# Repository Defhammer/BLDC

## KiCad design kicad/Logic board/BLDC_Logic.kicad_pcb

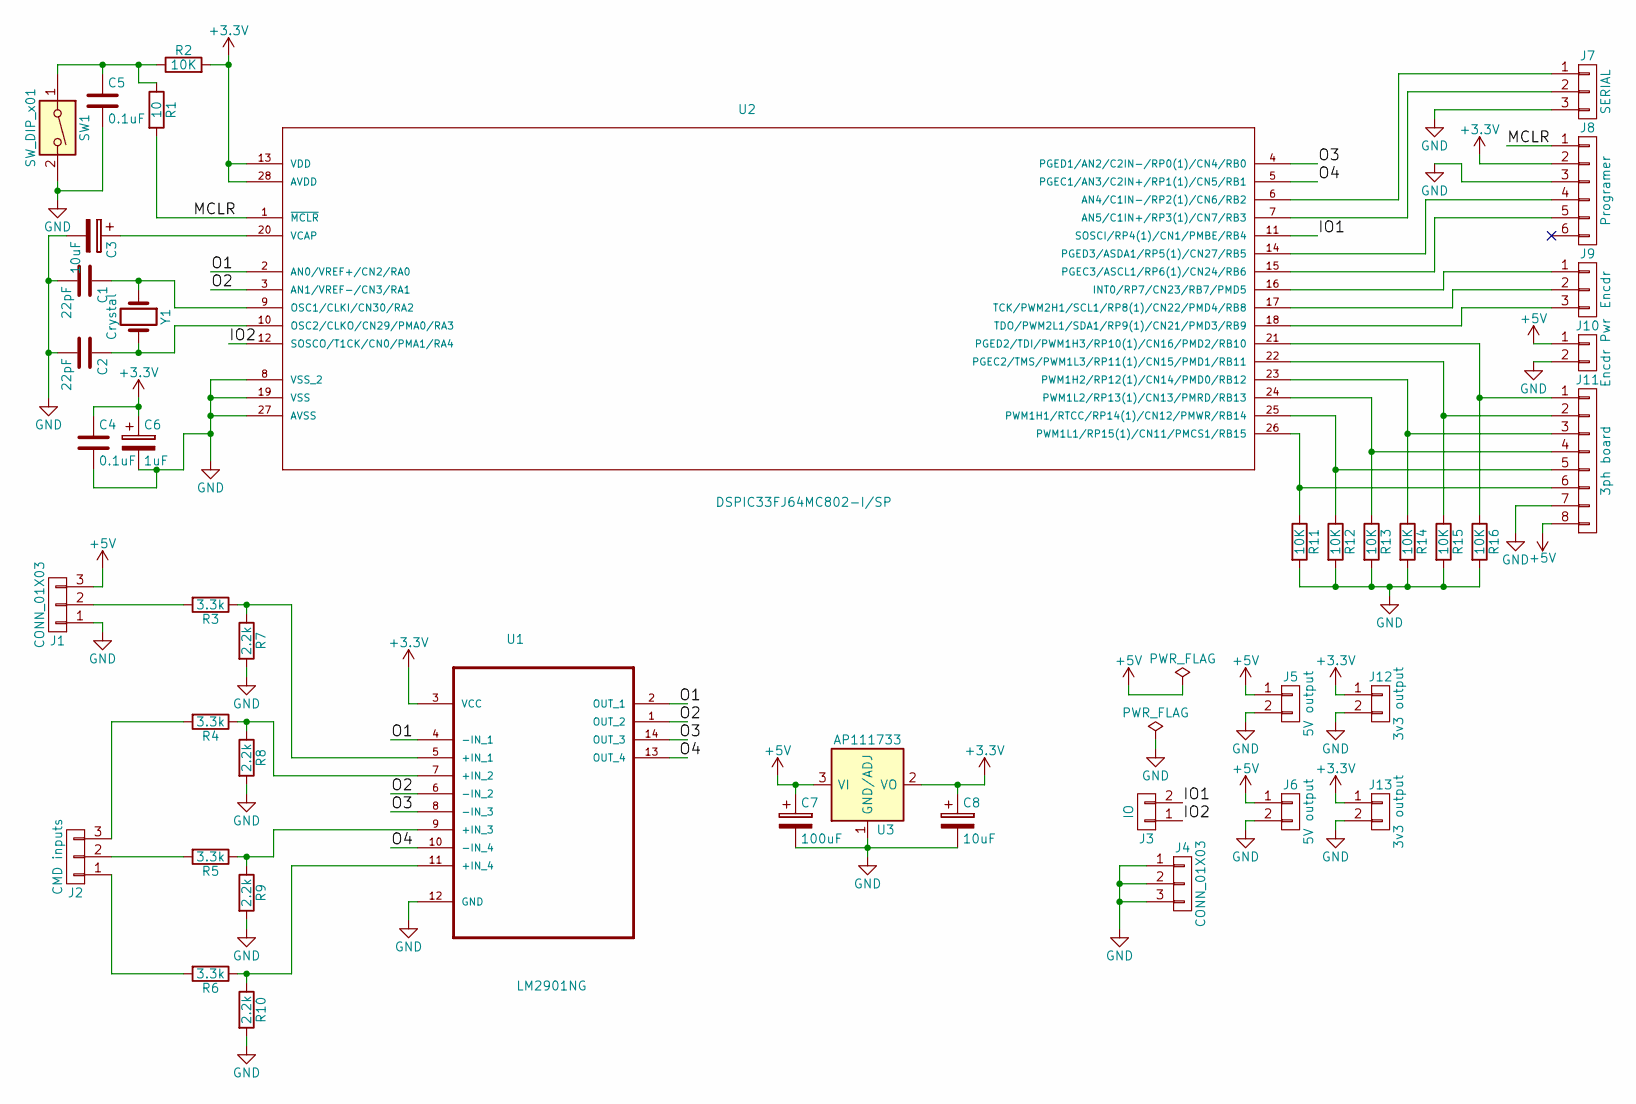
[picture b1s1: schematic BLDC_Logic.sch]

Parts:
C1, C2: 22pF; C_Disc_D3.0mm_W1.6mm_P2.50mm
C3: 10uF; CP_Radial_D4.0mm_P1.50mm
C4, C5: 0.1uF; C_Disc_D3.0mm_W2.0mm_P2.50mm
C6: 1uF; CP_Radial_D4.0mm_P2.00mm
C7: 100uF; CP_Radial_D6.3mm_P2.50mm
C8: 10uF; CP_Radial_D4.0mm_P2.00mm
J1, J4: CONN_01X03; Pin_Header_Straight_1x03_Pitch2.54mm
J2: CMD inputs; Pin_Header_Straight_1x03_Pitch2.54mm
J3: IO; Pin_Header_Straight_1x02_Pitch2.54mm
J5, J6: 5V output; Pin_Header_Straight_1x02_Pitch2.54mm
J7: SERIAL; Pin_Header_Straight_1x03_Pitch2.54mm
J8: Programer; Pin_Header_Straight_1x06_Pitch2.54mm
J9: Encdr; Pin_Header_Straight_1x03_Pitch2.54mm
J10: Encdr Pwr; Pin_Header_Straight_1x02_Pitch2.54mm
J11: 3ph board; Pin_Header_Straight_1x08_Pitch2.54mm
J12, J13: 3v3 output; Pin_Header_Straight_1x02_Pitch2.54mm
R1: 10; R_Axial_DIN0204_L3.6mm_D1.6mm_P7.62mm_Horizontal
R2, R11, R12, R13, R14, R15, R16: 10K; R_Axial_DIN0204_L3.6mm_D1.6mm_P7.62mm_Horizontal
R3, R4, R5, R6: 3.3k; R_Axial_DIN0204_L3.6mm_D1.6mm_P7.62mm_Horizontal
R7, R8, R9, R10: 2.2k; R_Axial_DIN0204_L3.6mm_D1.6mm_P7.62mm_Horizontal
SW1: SW_DIP_x01; SW_PUSH_6mm
U1: LM2901NG; DIP-14_W7.62mm
U2: DSPIC33FJ64MC802-I/SP; DIP254P762X508-28
U3: AP111733; TO-220_Vertical
Y1: Crystal; Crystal_HC49-U_Vertical

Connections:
+3V3: C4.1, C6.1, C8.1, J8.2, J12.1, J13.1, R2.2, U1.3 (VCC), U2.13 (VDD), U2.28 (AVDD), U3.2 (VO), U3.4 (VO)
+5V: C7.1, J1.3, J5.1, J6.1, J10.1, J11.8, U3.3 (VI)
/IO1: J3.2, U2.11 (SOSCI/RP4(1)/CN1/PMBE/RB4)
/IO2: J3.1, U2.12 (SOSCO/T1CK/CN0/PMA1/RA4)
/MCLR: J8.1, R1.2, U2.1 (~MCLR)
/O1: U1.2 (OUT_1), U1.4 (-IN_1), U2.2 (AN0/VREF+/CN2/RA0)
/O2: U1.1 (OUT_2), U1.6 (-IN_2), U2.3 (AN1/VREF-/CN3/RA1)
/O3: U1.8 (-IN_3), U1.14 (OUT_3), U2.4 (PGED1/AN2/C2IN-/RP0(1)/CN4/RB0)
/O4: U1.10 (-IN_4), U1.13 (OUT_4), U2.5 (PGEC1/AN3/C2IN+/RP1(1)/CN5/RB1)
GND: C1.2, C2.2, C3.2, C4.2, C5.2, C6.2, C7.2, C8.2, J1.1, J4.1, J4.2, J4.3, J5.2, J6.2, J7.3, J8.3, J10.2, J11.7, J12.2, J13.2, R7.2, R8.2, R9.2, R10.2, R11.2, R12.2, R13.2, R14.2, R15.2, R16.2, SW1.2, U1.12 (GND), U2.8 (VSS_2), U2.19 (VSS), U2.27 (AVSS), U3.1 (GND/ADJ)
unnamed: C1.1, U2.9 (OSC1/CLKI/CN30/RA2), Y1.1
unnamed: C2.1, U2.10 (OSC2/CLKO/CN29/PMA0/RA3), Y1.2
unnamed: C3.1, U2.20 (VCAP)
unnamed: C5.1, R1.1, R2.1, SW1.1
unnamed: J1.2, R3.2
unnamed: J2.1, R6.2
unnamed: J2.2, R5.2
unnamed: J2.3, R4.2
unnamed: J7.1, U2.6 (AN4/C1IN-/RP2(1)/CN6/RB2)
unnamed: J7.2, U2.7 (AN5/C1IN+/RP3(1)/CN7/RB3)
unnamed: J8.4, U2.14 (PGED3/ASDA1/RP5(1)/CN27/RB5)
unnamed: J8.5, U2.15 (PGEC3/ASCL1/RP6(1)/CN24/RB6)
unnamed: J9.1, U2.16 (INT0/RP7/CN23/RB7/PMD5)
unnamed: J9.2, U2.17 (TCK/PWM2H1/SCL1/RP8(1)/CN22/PMD4/RB8)
unnamed: J9.3, U2.18 (TDO/PWM2L1/SDA1/RP9(1)/CN21/PMD3/RB9)
unnamed: J11.1, R16.1, U2.21 (PGED2/TDI/PWM1H3/RP10(1)/CN16/PMD2/RB10)
unnamed: J11.2, R15.1, U2.22 (PGEC2/TMS/PWM1L3/RP11(1)/CN15/PMD1/RB11)
unnamed: J11.3, R14.1, U2.23 (PWM1H2/RP12(1)/CN14/PMD0/RB12)
unnamed: J11.4, R13.1, U2.24 (PWM1L2/RP13(1)/CN13/PMRD/RB13)
unnamed: J11.5, R12.1, U2.25 (PWM1H1/RTCC/RP14(1)/CN12/PMWR/RB14)
unnamed: J11.6, R11.1, U2.26 (PWM1L1/RP15(1)/CN11/PMCS1/RB15)
unnamed: R3.1, R7.1, U1.5 (+IN_1)
unnamed: R4.1, R8.1, U1.7 (+IN_2)
unnamed: R5.1, R9.1, U1.9 (+IN_3)
unnamed: R6.1, R10.1, U1.11 (+IN_4)

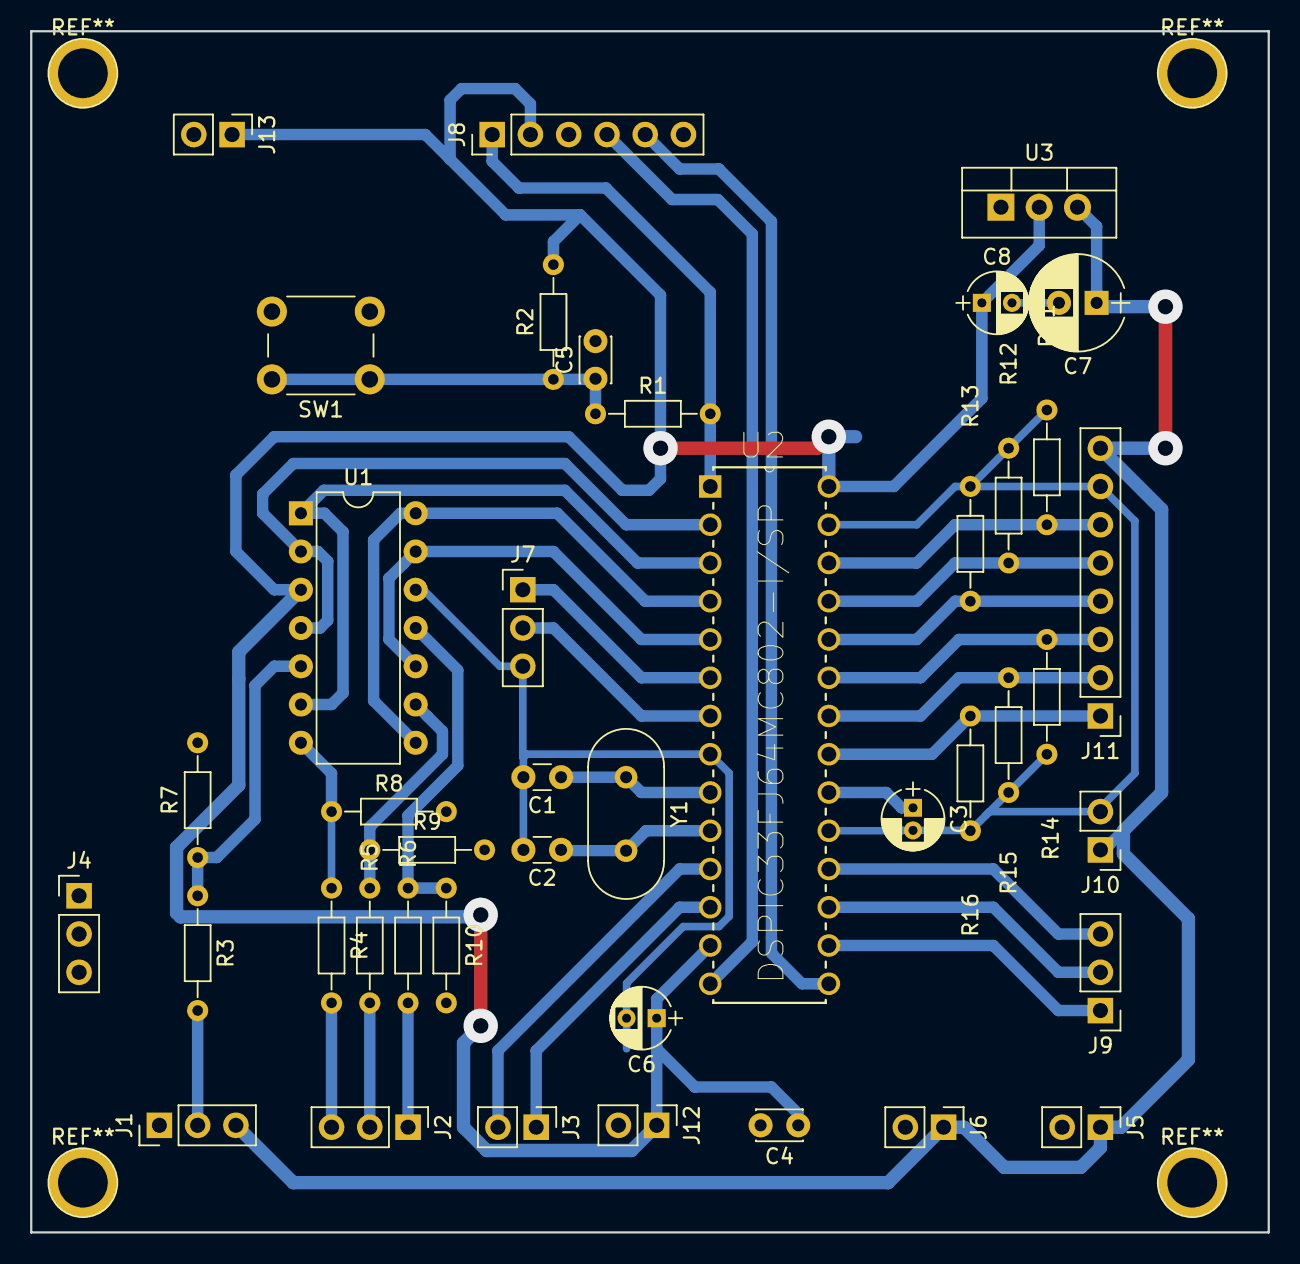
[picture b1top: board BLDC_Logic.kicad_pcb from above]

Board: 2 copper layers, 82.2 x 79.8 mm, 42 parts (0 on the bottom side), 35 nets.

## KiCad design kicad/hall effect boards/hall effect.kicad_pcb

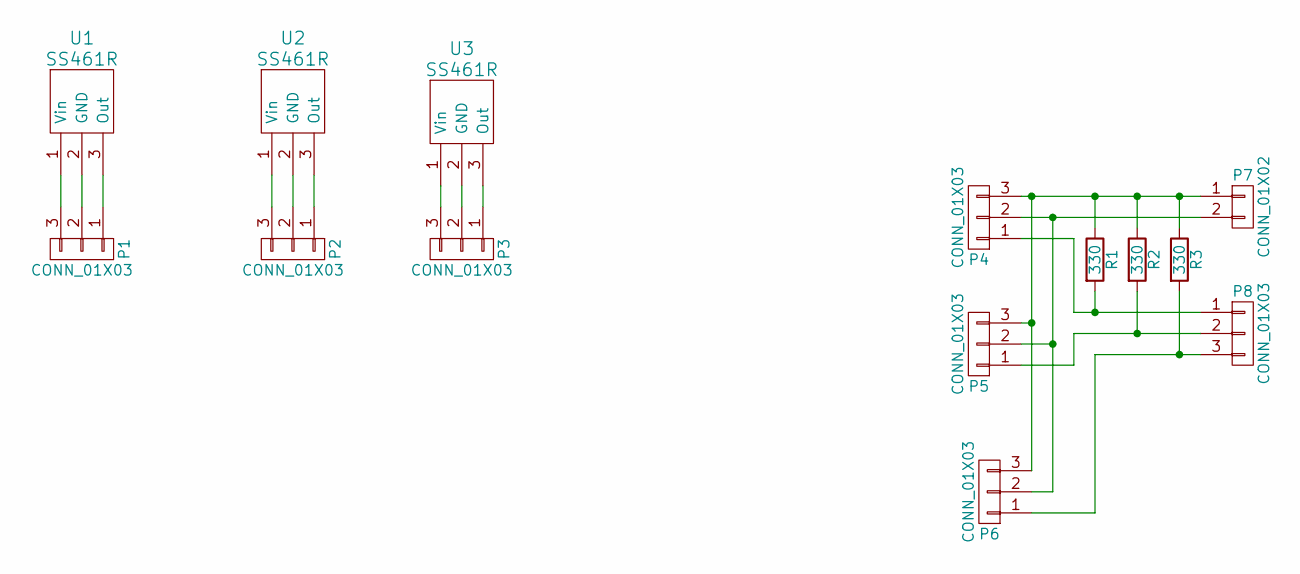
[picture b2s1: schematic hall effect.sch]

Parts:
P1, P2, P3, P4, P5, P6, P8: CONN_01X03; Pin_Header_Straight_1x03
P7: CONN_01X02; Pin_Header_Straight_1x02
R1, R2, R3: 330; Resistor_Horizontal_RM15mm
U1, U2, U3: SS461R; TO-92_Inline_Narrow_Oval

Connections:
unnamed: P1.1, U1.3 (Out)
unnamed: P1.2, U1.2 (GND)
unnamed: P1.3, U1.1 (Vin)
unnamed: P2.1, U2.3 (Out)
unnamed: P2.2, U2.2 (GND)
unnamed: P2.3, U2.1 (Vin)
unnamed: P3.1, U3.3 (Out)
unnamed: P3.2, U3.2 (GND)
unnamed: P3.3, U3.1 (Vin)
unnamed: P4.1, P8.1, R1.2
unnamed: P4.2, P5.2, P6.2, P7.2
unnamed: P4.3, P5.3, P6.3, P7.1, R1.1, R2.1, R3.1
unnamed: P5.1, P8.2, R2.2
unnamed: P6.1, P8.3, R3.2

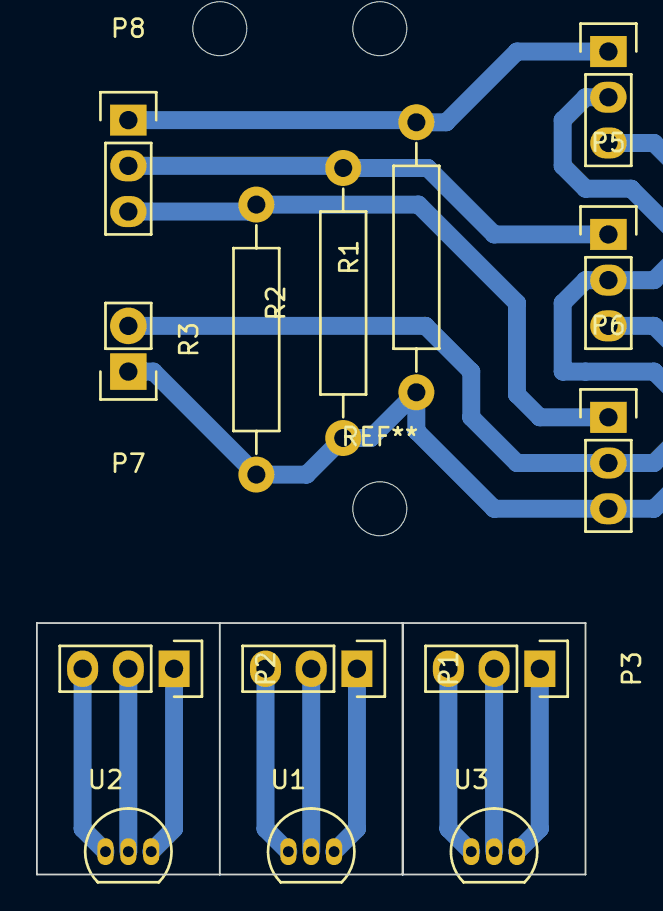
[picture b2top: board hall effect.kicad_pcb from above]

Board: 2 copper layers, 30.5 x 14.0 mm, 14 parts (0 on the bottom side), 14 nets.

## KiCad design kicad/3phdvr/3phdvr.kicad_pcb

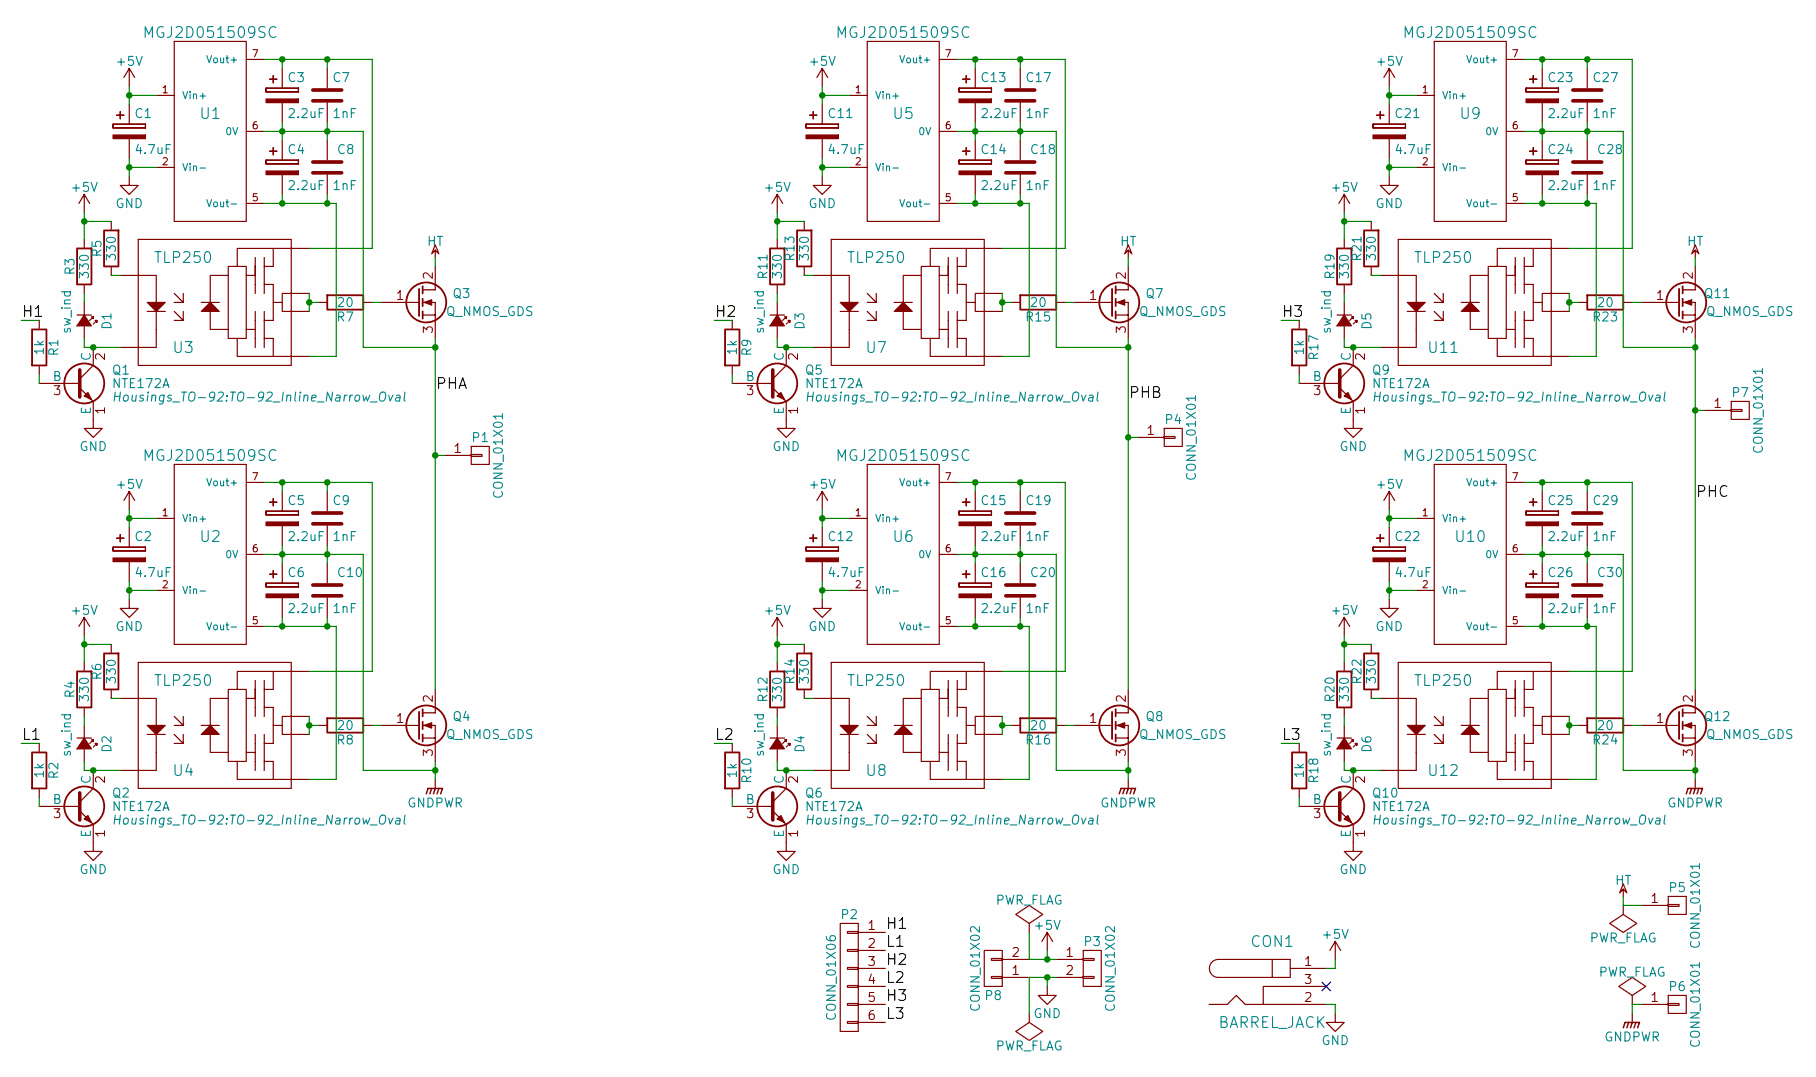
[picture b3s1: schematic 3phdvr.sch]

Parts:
C1, C2, C11, C12, C21, C22: 4.7uF; C_Radial_D5_L6_P2.5
C3, C4, C5, C6, C13, C14, C15, C16, C23, C24, C25, C26: 2.2uF; C_Radial_D5_L6_P2.5
C7, C8, C9, C10, C17, C18, C19, C20, C27, C28, C29, C30: 1nF; C_Disc_D3_P2.5
CON1: BARREL_JACK; Jack_2.1mm_male
D1, D2, D3, D4, D5, D6: sw_ind; LED-3MM
P1, P4, P5, P6, P7: CONN_01X01; SolderWirePad_single_3-25mmDrill
P2: CONN_01X06; Pin_Header_Straight_1x06
P3, P8: CONN_01X02; Pin_Header_Straight_1x02
Q1, Q2, Q5, Q6, Q9, Q10: NTE172A; TO-92_Inline_Narrow_Oval
Q3, Q4, Q7, Q8, Q11, Q12: Q_NMOS_GDS; TO-247_Horizontal_Neutral123_Reverse_largePads
R1, R2, R9, R10, R17, R18: 1k; Resistor_Horizontal_RM10mm
R3, R4, R5, R6, R11, R12, R13, R14, R19, R20, R21, R22: 330; Resistor_Horizontal_RM10mm
R7, R8, R15, R16, R23, R24: 20; Resistor_Horizontal_RM15mm
U1, U2, U5, U6, U9, U10: MGJ2D051509SC; 7-Module_(5leads)_MJ
U3, U4, U7, U8, U11, U12: TLP250; DIP-8_W7.62mm_LongPads

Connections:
+5V: C1.1, C2.1, C11.1, C12.1, C21.1, C22.1, CON1.1, P3.1, P8.2, R3.2, R4.2, R5.2, R6.2, R11.2, R12.2, R13.2, R14.2, R19.2, R20.2, R21.2, R22.2, U1.1 (Vin+), U2.1 (Vin+), U5.1 (Vin+), U6.1 (Vin+), U9.1 (Vin+), U10.1 (Vin+)
/H1: P2.1, R1.1
/H2: P2.3, R9.1
/H3: P2.5, R17.1
/L1: P2.2, R2.1
/L2: P2.4, R10.1
/L3: P2.6, R18.1
/PHA: C3.2, C4.1, C7.2, C8.1, P1.1, Q3.3 (S), Q4.2 (D), U1.6 (0V)
/PHB: C13.2, C14.1, C17.2, C18.1, P4.1, Q7.3 (S), Q8.2 (D), U5.6 (0V)
/PHC: C23.2, C24.1, C27.2, C28.1, P7.1, Q11.3 (S), Q12.2 (D), U9.6 (0V)
GND: C1.2, C2.2, C11.2, C12.2, C21.2, C22.2, CON1.2, P3.2, P8.1, Q1.1 (E), Q2.1 (E), Q5.1 (E), Q6.1 (E), Q9.1 (E), Q10.1 (E), U1.2 (Vin-), U2.2 (Vin-), U5.2 (Vin-), U6.2 (Vin-), U9.2 (Vin-), U10.2 (Vin-)
GNDPWR: C5.2, C6.1, C9.2, C10.1, C15.2, C16.1, C19.2, C20.1, C25.2, C26.1, C29.2, C30.1, P6.1, Q4.3 (S), Q8.3 (S), Q12.3 (S), U2.6 (0V), U6.6 (0V), U10.6 (0V)
HT: P5.1, Q3.2 (D), Q7.2 (D), Q11.2 (D)
unnamed: C3.1, C7.1, U1.7 (Vout+), U3.8
unnamed: C4.2, C8.2, U1.5 (Vout-), U3.5
unnamed: C5.1, C9.1, U2.7 (Vout+), U4.8
unnamed: C6.2, C10.2, U2.5 (Vout-), U4.5
unnamed: C13.1, C17.1, U5.7 (Vout+), U7.8
unnamed: C14.2, C18.2, U5.5 (Vout-), U7.5
unnamed: C15.1, C19.1, U6.7 (Vout+), U8.8
unnamed: C16.2, C20.2, U6.5 (Vout-), U8.5
unnamed: C23.1, C27.1, U9.7 (Vout+), U11.8
unnamed: C24.2, C28.2, U9.5 (Vout-), U11.5
unnamed: C25.1, C29.1, U10.7 (Vout+), U12.8
unnamed: C26.2, C30.2, U10.5 (Vout-), U12.5
unnamed: D1.1 (K), R3.1
unnamed: D1.2 (A), Q1.2 (C), U3.3
unnamed: D2.1 (K), R4.1
unnamed: D2.2 (A), Q2.2 (C), U4.3
unnamed: D3.1 (K), R11.1
unnamed: D3.2 (A), Q5.2 (C), U7.3
unnamed: D4.1 (K), R12.1
unnamed: D4.2 (A), Q6.2 (C), U8.3
unnamed: D5.1 (K), R19.1
unnamed: D5.2 (A), Q9.2 (C), U11.3
unnamed: D6.1 (K), R20.1
unnamed: D6.2 (A), Q10.2 (C), U12.3
unnamed: Q1.3 (B), R1.2
unnamed: Q2.3 (B), R2.2
unnamed: Q3.1 (G), R7.1
unnamed: Q4.1 (G), R8.1
unnamed: Q5.3 (B), R9.2
unnamed: Q6.3 (B), R10.2
unnamed: Q7.1 (G), R15.1
unnamed: Q8.1 (G), R16.1
unnamed: Q9.3 (B), R17.2
unnamed: Q10.3 (B), R18.2
unnamed: Q11.1 (G), R23.1
unnamed: Q12.1 (G), R24.1
unnamed: R5.1, U3.2
unnamed: R6.1, U4.2
unnamed: R7.2, U3.6, U3.7
unnamed: R8.2, U4.6, U4.7
unnamed: R13.1, U7.2
unnamed: R14.1, U8.2
unnamed: R15.2, U7.6, U7.7
unnamed: R16.2, U8.6, U8.7
unnamed: R21.1, U11.2
unnamed: R22.1, U12.2
unnamed: R23.2, U11.6, U11.7
unnamed: R24.2, U12.6, U12.7

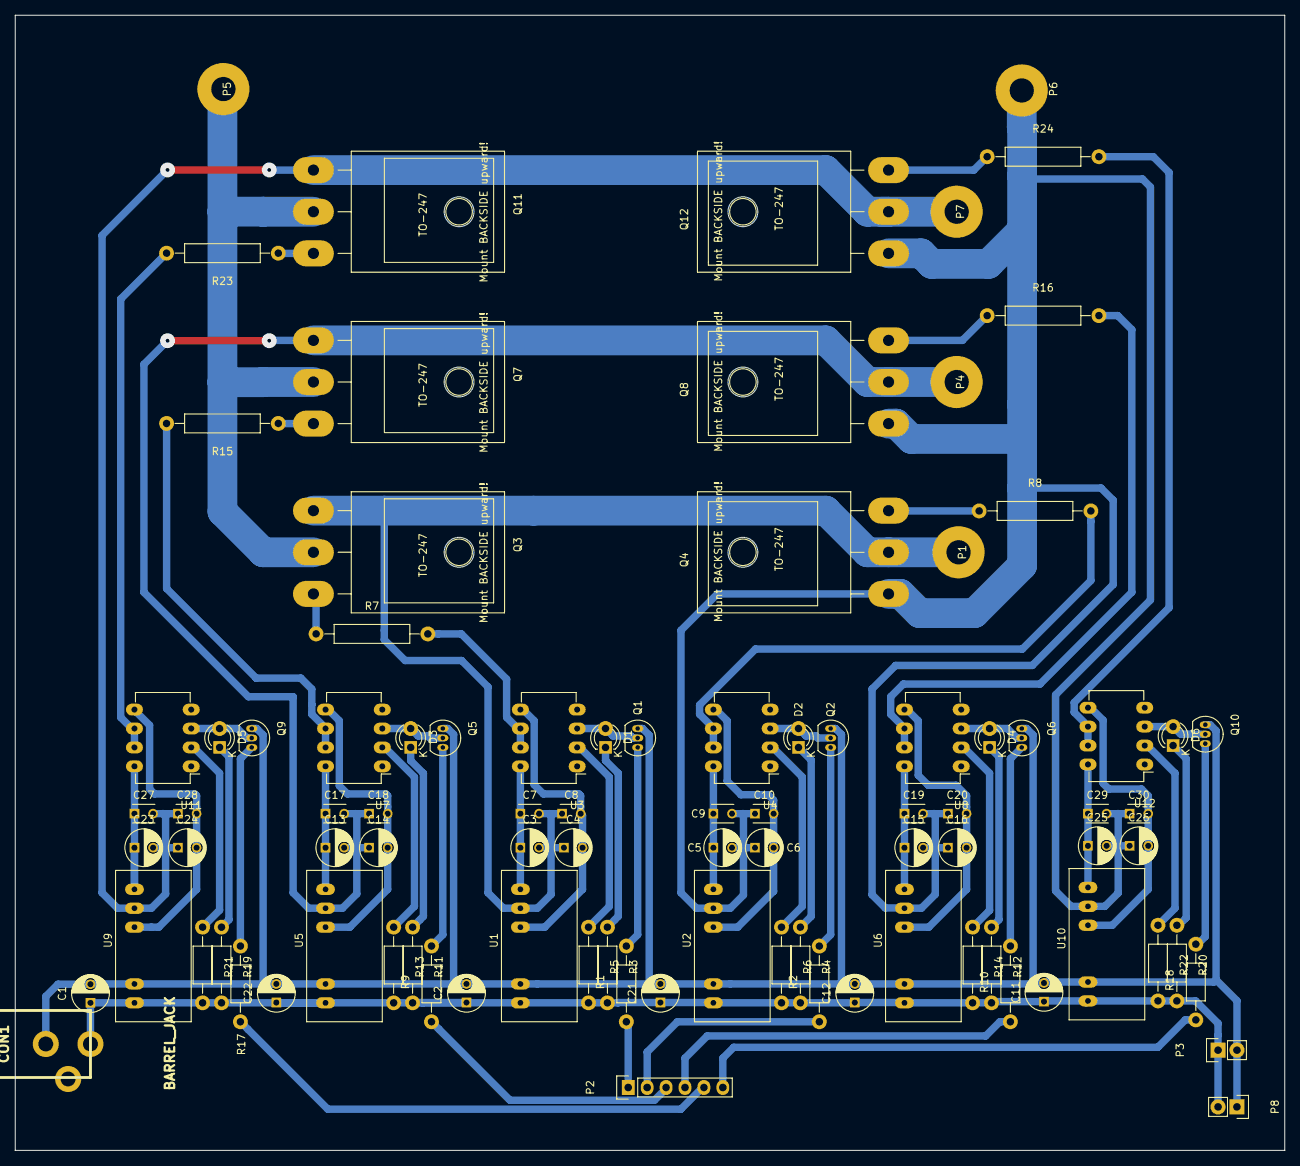
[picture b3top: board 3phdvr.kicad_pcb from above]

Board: 2 copper layers, 170.4 x 152.4 mm, 93 parts (0 on the bottom side), 61 nets.

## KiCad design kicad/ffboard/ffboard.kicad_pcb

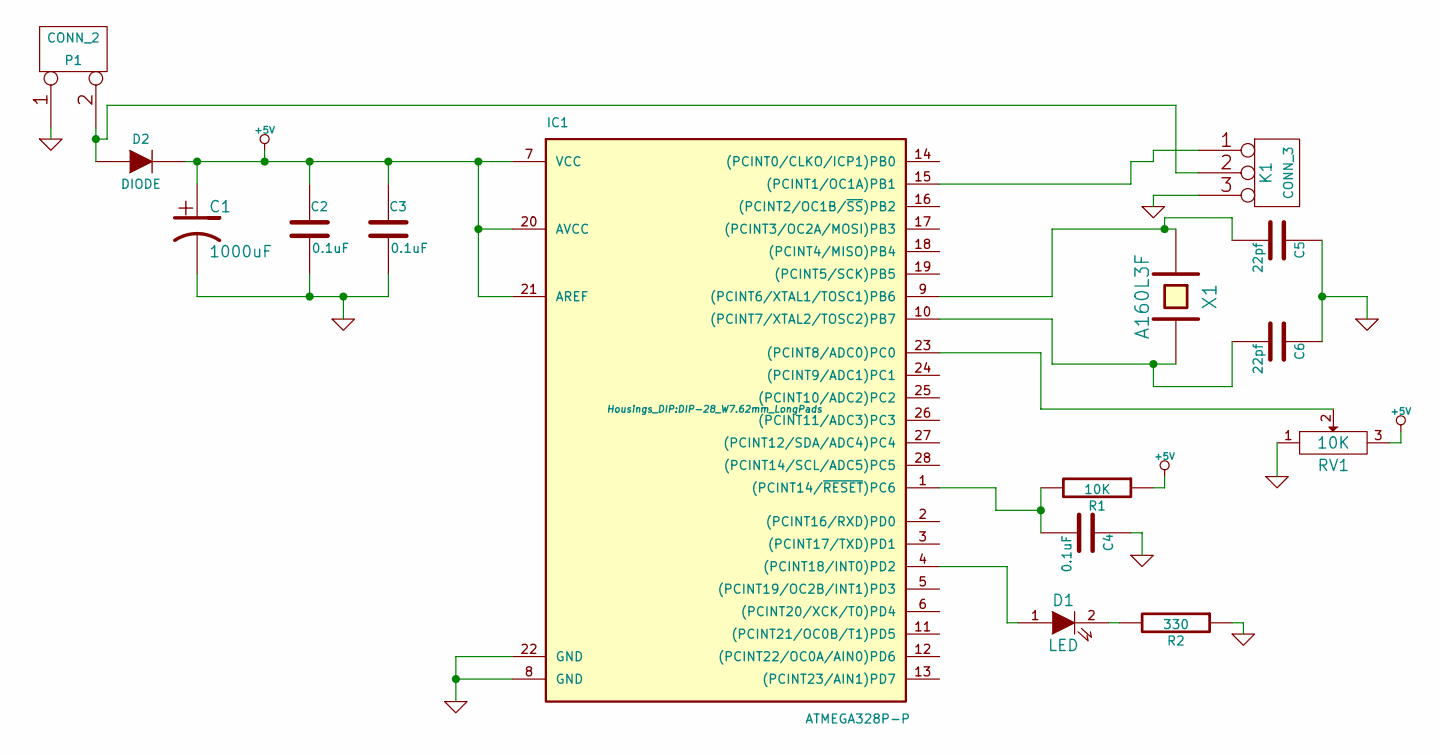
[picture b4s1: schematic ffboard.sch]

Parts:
C1: 1000uF; C_Radial_D10_L16_P5
C2, C3, C4: 0.1uF; C_Disc_D6_P5
C5, C6: 22pf; C_Disc_D3_P2.5
D1: LED; LED-5MM
D2: DIODE; Diode_DO-41_SOD81_Horizontal_RM10
IC1: ATMEGA328P-P; DIP-28_W7.62mm_LongPads
K1: CONN_3; Pin_Header_Angled_1x03
P1: CONN_2; TE_3.5mm_terminal_block_2pos
R1: 10K; Resistor_Horizontal_RM10mm
R2: 330; Resistor_Horizontal_RM10mm
RV1: 10K; Potentiometer_Bourns_3296W_3-8Zoll_Inline_ScrewUp
X1: A160L3F; HC-18UV

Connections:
+5V: C1.1, C2.1, C3.1, D2.2 (K), IC1.7 (VCC), IC1.20 (AVCC), IC1.21 (AREF), R1.1, RV1.3
GND: C1.2, C2.2, C3.2, C4.1, C5.1, C6.1, IC1.8 (GND), IC1.22 (GND), K1.3, P1.1, R2.1, RV1.1
unnamed: C4.2, IC1.1 ((PCINT14/~RESET~)PC6), R1.2
unnamed: C5.2, IC1.9 ((PCINT6/XTAL1/TOSC1)PB6), X1.1
unnamed: C6.2, IC1.10 ((PCINT7/XTAL2/TOSC2)PB7), X1.2
unnamed: D1.1 (A), IC1.4 ((PCINT18/INT0)PD2)
unnamed: D1.2 (K), R2.2
unnamed: D2.1 (A), K1.2 (PM), P1.2 (PM)
unnamed: IC1.15 ((PCINT1/OC1A)PB1), K1.1
unnamed: IC1.23 ((PCINT8/ADC0)PC0), RV1.2

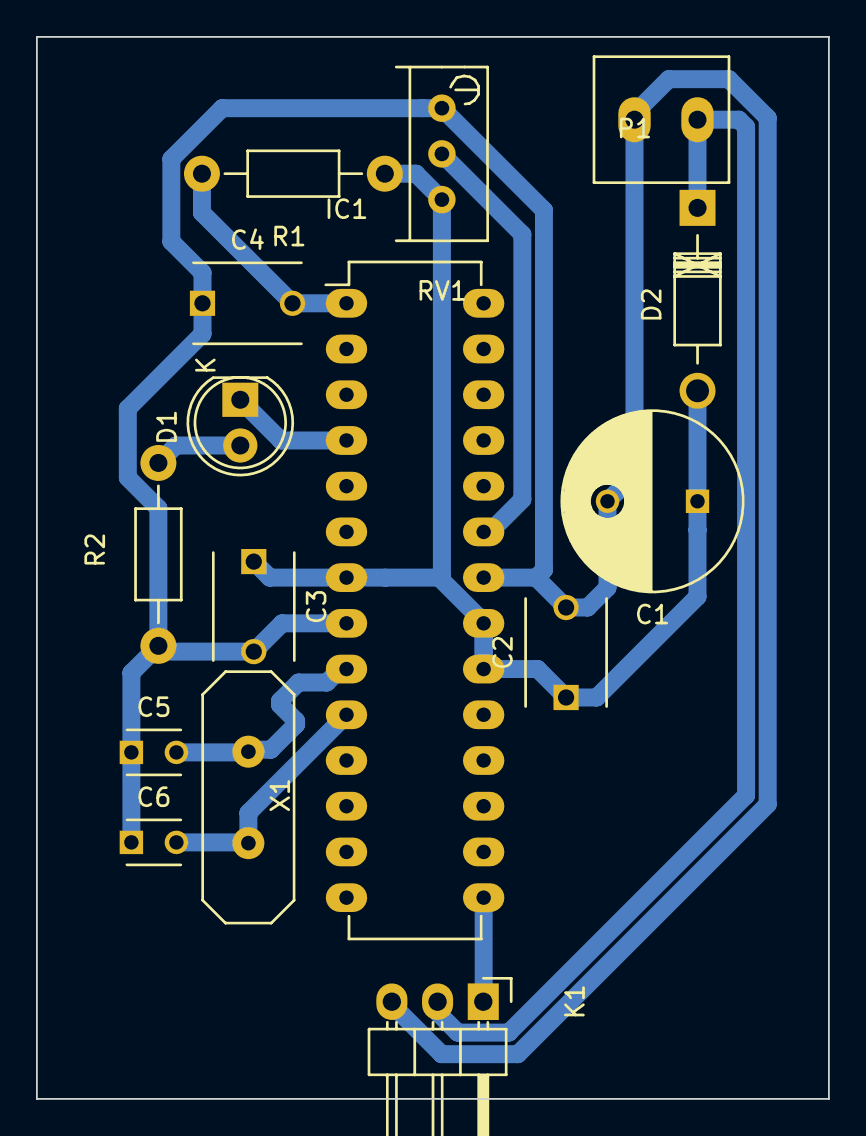
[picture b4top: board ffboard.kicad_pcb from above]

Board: 2 copper layers, 44.0 x 59.0 mm, 15 parts (0 on the bottom side), 10 nets.

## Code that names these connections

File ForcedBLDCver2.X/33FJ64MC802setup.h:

/* Microchip Technology Inc. and its subsidiaries.  You may use this software 
 * and any derivatives exclusively with Microchip products. 
 * 
 * THIS SOFTWARE IS SUPPLIED BY MICROCHIP "AS IS".  NO WARRANTIES, WHETHER 
 * EXPRESS, IMPLIED OR STATUTORY, APPLY TO THIS SOFTWARE, INCLUDING ANY IMPLIED 
 * WARRANTIES OF NON-INFRINGEMENT, MERCHANTABILITY, AND FITNESS FOR A 
 * PARTICULAR PURPOSE, OR ITS INTERACTION WITH MICROCHIP PRODUCTS, COMBINATION 
 * WITH ANY OTHER PRODUCTS, OR USE IN ANY APPLICATION. 
 *
 * IN NO EVENT WILL MICROCHIP BE LIABLE FOR ANY INDIRECT, SPECIAL, PUNITIVE, 
 * INCIDENTAL OR CONSEQUENTIAL LOSS, DAMAGE, COST OR EXPENSE OF ANY KIND 
 * WHATSOEVER RELATED TO THE SOFTWARE, HOWEVER CAUSED, EVEN IF MICROCHIP HAS 
 * BEEN ADVISED OF THE POSSIBILITY OR THE DAMAGES ARE FORESEEABLE.  TO THE 
 * FULLEST EXTENT ALLOWED BY LAW, MICROCHIP'S TOTAL LIABILITY ON ALL CLAIMS 
 * IN ANY WAY RELATED TO THIS SOFTWARE WILL NOT EXCEED THE AMOUNT OF FEES, IF 
 * ANY, THAT YOU HAVE PAID DIRECTLY TO MICROCHIP FOR THIS SOFTWARE.
 *
 * MICROCHIP PROVIDES THIS SOFTWARE CONDITIONALLY UPON YOUR ACCEPTANCE OF THESE 
 * TERMS. 
 */

/* 
 * File:   
 * Author: 
 * Comments:
 * Revision history: 
 */

// This is a guard condition so that contents of this file are not included
// more than once.  
#ifndef XC_HEADER_TEMPLATE_H
#define	XC_HEADER_TEMPLATE_H

// DSPIC33FJ64MC802 Configuration Bit Settings

// 'C' source line config statements

// FBS
#pragma config BWRP = WRPROTECT_OFF     // Boot Segment Write Protect (Boot Segment may be written)
#pragma config BSS = NO_FLASH           // Boot Segment Program Flash Code Protection (No Boot program Flash segment)
#pragma config RBS = NO_RAM             // Boot Segment RAM Protection (No Boot RAM)

// FSS
#pragma config SWRP = WRPROTECT_OFF     // Secure Segment Program Write Protect (Secure segment may be written)
#pragma config SSS = NO_FLASH           // Secure Segment Program Flash Code Protection (No Secure Segment)
#pragma config RSS = NO_RAM             // Secure Segment Data RAM Protection (No Secure RAM)

// FGS
#pragma config GWRP = OFF               // General Code Segment Write Protect (User program memory is not write-protected)
#pragma config GSS = OFF                // General Segment Code Protection (User program memory is not code-protected)

// FOSCSEL
#pragma config FNOSC = PRIPLL          // Oscillator Mode (Primary Oscillator (XT, HS, EC) w/ PLL)
#pragma config IESO = OFF               // Internal External Switch Over Mode (Start-up device with FRC, then automatically switch to user-selected oscillator source when ready)

// FOSC
#pragma config POSCMD = HS              // Primary Oscillator Source (HS Oscillator Mode)
#pragma config OSCIOFNC = OFF           // OSC2 Pin Function (OSC2 pin has clock out function)
#pragma config IOL1WAY = ON             // Peripheral Pin Select Configuration (Allow Only One Re-configuration)
#pragma config FCKSM = CSDCMD           // Clock Switching and Monitor (Both Clock Switching and Fail-Safe Clock Monitor are disabled)

// FWDT
#pragma config WDTPOST = PS32768        // Watchdog Timer Postscaler (1:32,768)
#pragma config WDTPRE = PR128           // WDT Prescaler (1:128)
#pragma config WINDIS = OFF             // Watchdog Timer Window (Watchdog Timer in Non-Window mode)
#pragma config FWDTEN = OFF             // Watchdog Timer Enable (Watchdog timer enabled/disabled by user software)

// FPOR
#pragma config FPWRT = PWR128           // POR Timer Value (128ms)
#pragma config ALTI2C = OFF             // Alternate I2C  pins (I2C mapped to SDA1/SCL1 pins)
#pragma config LPOL = ON                // Motor Control PWM Low Side Polarity bit (PWM module low side output pins have active-high output polarity)
#pragma config HPOL = ON                // Motor Control PWM High Side Polarity bit (PWM module high side output pins have active-high output polarity)
#pragma config PWMPIN = OFF             // Motor Control PWM Module Pin Mode bit (PWM module pins controlled by PWM module at device Reset)

// FICD
#pragma config ICS = PGD3               // Comm Channel Select (Communicate on PGC3/EMUC3 and PGD3/EMUD3)
#pragma config JTAGEN = OFF             // JTAG Port Enable (JTAG is Disabled)

// #pragma config statements should precede project file includes.
// Use project enums instead of #define for ON and OFF.

#include <xc.h> // include processor files - each processor file is guarded.  

void initClk () {
    
    CLKDIVbits.PLLPRE = 6;
    PLLFBDbits.PLLDIV=78;
    CLKDIVbits.PLLPOST =0x0;
}

void initIO() {
    /*contains the  overall pinout as defined in the PCB design.
     PWM */
    
    
    
    //RAx defined as input RBx defined as output
    TRISA=0xFFFF;
    TRISB =0x0000;
    TRISAbits.TRISA4 = 1;
    
    //AN0 for detecting current
    AD1PCFGL =0x0000;
    AD1PCFGLbits.PCFG0=1;  //AN0 for current sense.
   
    //RA1- spindle enable - input - Change notification enabled
    CNEN1bits.CN3IE = 1;
    //RB0-spindle Direction -input- Change notification enabled
    CNEN1bits.CN4IE =1;
    TRISBbits.TRISB0 = 1;
    
    //RB1- spindle speed - input -input capture
    TRISBbits.TRISB1 = 1;
    RPINR7bits.IC1R = 1;
    
    //RB2 - UART tx
    TRISBbits.TRISB2 = 0;   //RB2 output
    RPOR1bits.RP3R = 3;     //UART1 TX
    
    //RB3 -UART RX
    TRISBbits.TRISB3 = 1;   //RB3 input
    RPINR18bits.U1RXR = 2;  //UART1 RX
    
    TRISBbits.TRISB4 = 0;
    // pin Rb5 and Rb7 reserved for ICSP
    
    //encoder input pins 
    TRISBbits.TRISB7 = 1;
    TRISBbits.TRISB8 = 1;
    TRISBbits.TRISB9 = 1;
    
    RPINR14bits.QEA1R =0x07;    //PhA QEI1
    RPINR14bits.QEB1R =0x08;    //PhB QEI1
    RPINR15bits.INDX1R=0x09;    //INDX QEI1 
            
    //PWM pins Under control of MPWM1 through config bits and TRISB
  
    
}

#endif	/* XC_HEADER_TEMPLATE_H */

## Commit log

2017-02-14 initial BLDC project of all files
    this is the start of the repository
2017-02-14 cleanup the build files and build errors
2017-02-15 put in the commutation locations bassed on a 2048 PPR encoder.
    reorganized the array for better readability
2017-02-15 fixed commutate range
2017-02-16 MPLABX modicaticions
    looks like some modifcations from MPLABx when moving to github
2017-03-14 cleaned up code so it can compile (pointer to array)
2017-04-25 Logic board added
    BLDC logic board Version 2 was added. sechmatic is mostly done
2017-04-25 get pdf in
    get datasheet for Microcontroller in
2017-04-25 trying to fix commiting
2017-04-25 doing some cleanup
2017-04-25 more cleanup
2017-04-25 added MCLR Circuit
    added MCLR circuit based on version 1 board
2017-04-26 finished schmatic beggining layout
    finished the schmatic of Logic board, layout is incomplete
2017-04-26 continued layout work
2017-04-26 comit existing changes
2017-04-28 Finished PCB switched 3ph board connector
    completed the PCB layout of the board, changed from a 6 pole connect to
    an 8 pole to intergrate 6 pwm signals and 5 volt power into one
    connector, replacing the sperate 2 pole power connector. ( mountiong
    holes are still needed
2017-04-28 add mounting holes change page size from A4 to Letter
2017-04-28 changed the botton to better fit components. thickened traces for easier PCB fabrication. did some minor rerouting for smaller current loops.
2017-04-28 did some saving
2017-04-29 removed Drill file and grid offsets
    some clean up as well as testing of github to make sure everything works
2017-04-30 removed target indicator of PCB
2017-05-11 added speed function
    added a example speed function that compiles correctly (still need to
    add input detection, and pid)
2017-05-26 added IO assignments tuned CPU clock
    worked to overcome Clock issues and added IO assigments that matched up
    to the PCB
2017-05-26 fixing thing and clean up
2017-05-26 updated from master
2017-05-26 cleaned up a closed projects
2017-05-27 place all basic parts of BLDC_encoder_firmware
    put in most code into DLBD_encoder_firmware transfer supporting files
    built in ForcedBLDCver2 to BLDC_encoder_firmware
